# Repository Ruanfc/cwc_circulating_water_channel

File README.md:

# cwc_circulating_water_channel

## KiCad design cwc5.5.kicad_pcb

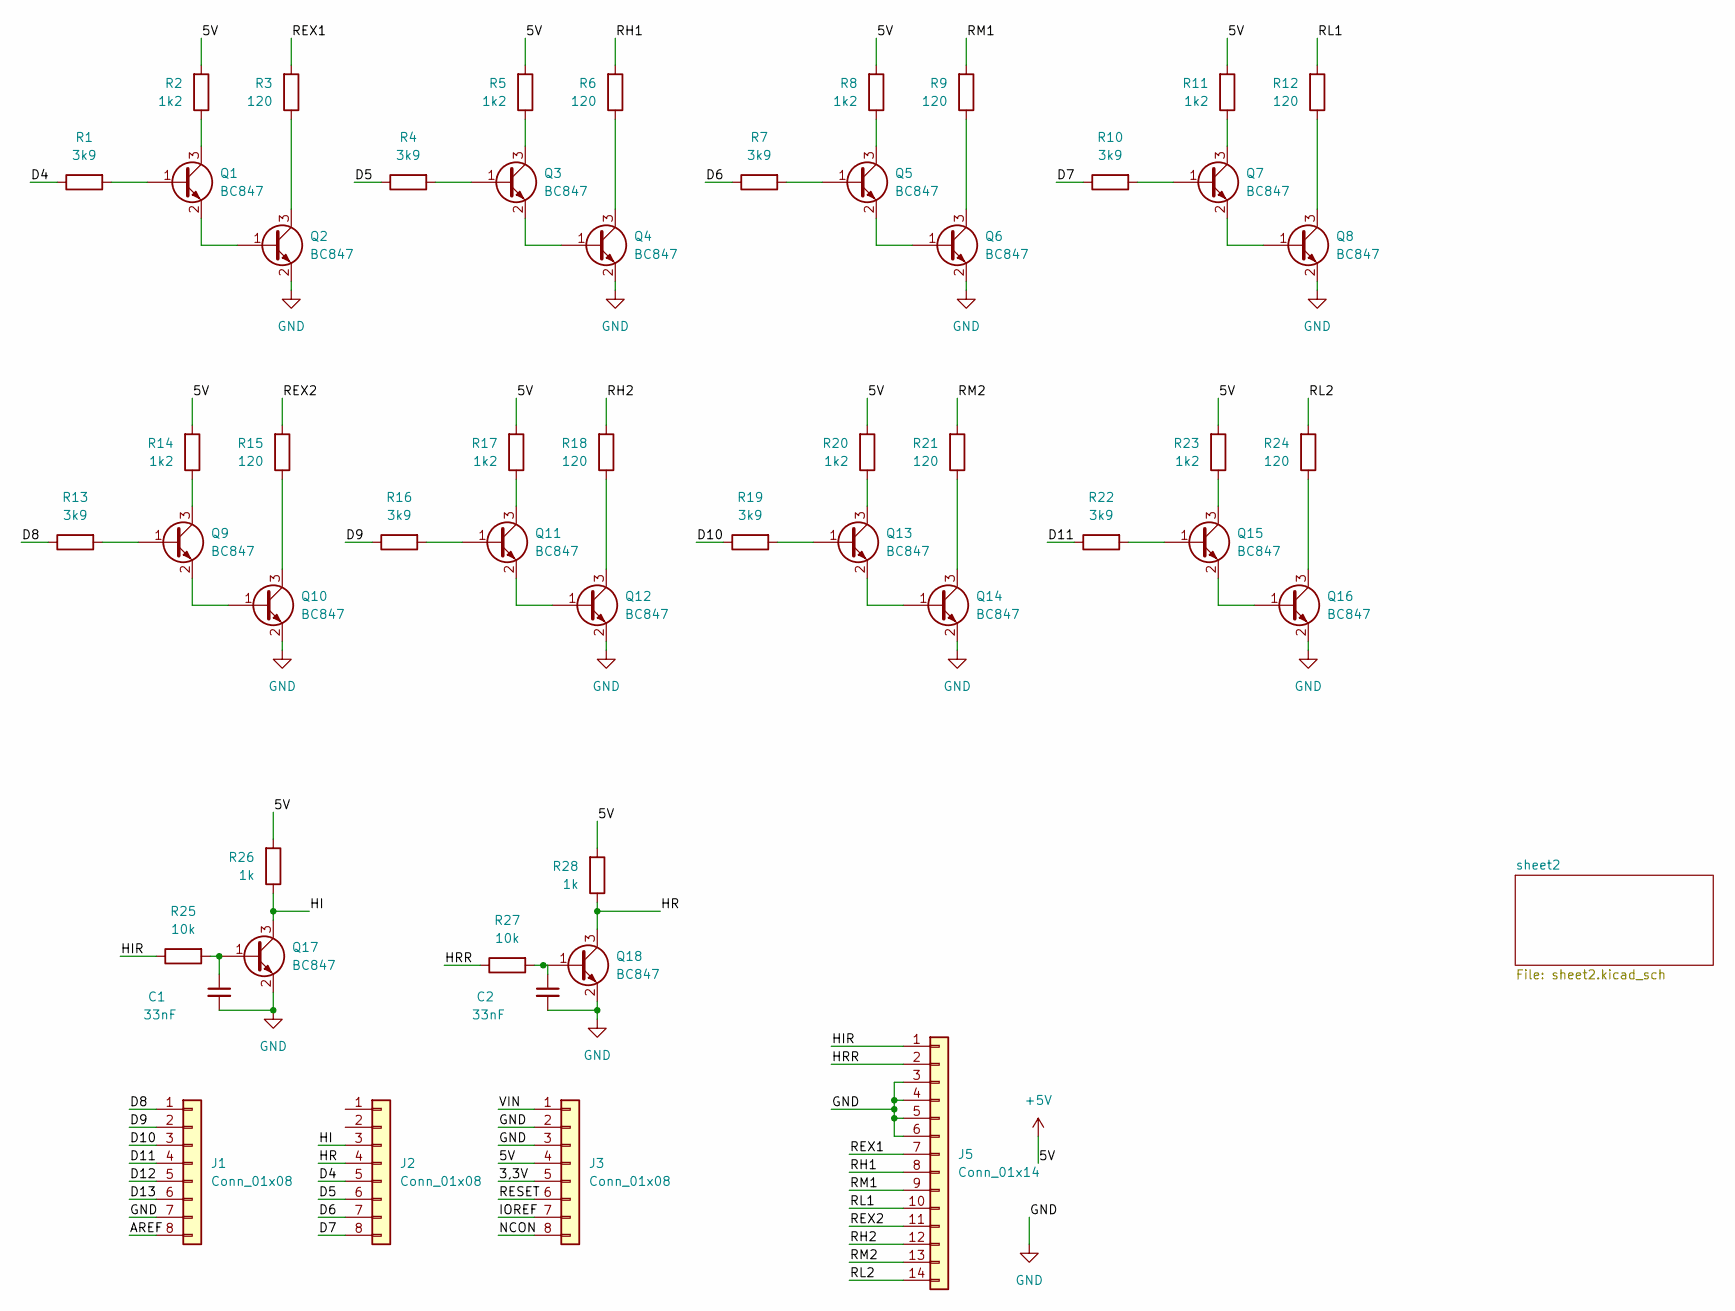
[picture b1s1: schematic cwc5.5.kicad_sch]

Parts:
C1, C2: 33nF; C_1206_3216Metric_Pad1.33x1.80mm_HandSolder
J1, J2, J3: Conn_01x08; PinHeader_1x08_P2.54mm_Vertical
J5: Conn_01x14; PinHeader_1x14_P2.54mm_Vertical
Q1, Q2, Q3, Q4, Q5, Q6, Q7, Q8, Q9, Q10, Q11, Q12, Q13, Q14, Q15, Q16, Q17, Q18: BC847; SOT-23_Handsoldering
R1, R4, R7, R10, R13, R16, R19, R22: 3k9; R_1206_3216Metric_Pad1.30x1.75mm_HandSolder
R2, R5, R8, R11, R14, R17, R20, R23: 1k2; R_1206_3216Metric_Pad1.30x1.75mm_HandSolder
R3, R6, R9, R12, R15, R18, R21, R24: 120; R_1206_3216Metric_Pad1.30x1.75mm_HandSolder
R25, R27: 10k; R_1206_3216Metric_Pad1.30x1.75mm_HandSolder
R26, R28: 1k; R_1206_3216Metric_Pad1.30x1.75mm_HandSolder

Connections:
+5V: J3.4, R2.2, R5.2, R8.2, R11.2, R14.2, R17.2, R20.2, R23.2, R26.2, R28.2
/3,3V: J3.5
/AREF: J1.8
/D4: J2.5, R1.1
/D5: J2.6, R4.1
/D6: J2.7, R7.1
/D7: J2.8, R10.1
/D8: J1.1, R13.1
/D9: J1.2, R16.1
/D10: J1.3, R19.1
/D11: J1.4, R22.1
/D12: J1.5
/D13: J1.6
/HI: J2.3, Q17.3 (C), R26.1
/HIR: J5.1, R25.1
/HR: J2.4, Q18.3 (C), R28.1
/HRR: J5.2, R27.1
/IOREF: J3.7
/NCON: J3.8
/RESET: J3.6
/REX1: J5.7, R3.2
/REX2: J5.11, R15.2
/RH1: J5.8, R6.2
/RH2: J5.12, R18.2
/RL1: J5.10, R12.2
/RL2: J5.14, R24.2
/RM1: J5.9, R9.2
/RM2: J5.13, R21.2
/VIN: J3.1
GND: C1.2, C2.2, J1.7, J3.2, J3.3, J5.3, J5.4, J5.5, J5.6, Q2.2 (E), Q4.2 (E), Q6.2 (E), Q8.2 (E), Q10.2 (E), Q12.2 (E), Q14.2 (E), Q16.2 (E), Q17.2 (E), Q18.2 (E); also elsewhere on the board
unnamed: C1.1, Q17.1 (B), R25.2
unnamed: C2.1, Q18.1 (B), R27.2
unnamed: Q1.1 (B), R1.2
unnamed: Q1.2 (E), Q2.1 (B)
unnamed: Q1.3 (C), R2.1
unnamed: Q2.3 (C), R3.1
unnamed: Q3.1 (B), R4.2
unnamed: Q3.2 (E), Q4.1 (B)
unnamed: Q3.3 (C), R5.1
unnamed: Q4.3 (C), R6.1
unnamed: Q5.1 (B), R7.2
unnamed: Q5.2 (E), Q6.1 (B)
unnamed: Q5.3 (C), R8.1
unnamed: Q6.3 (C), R9.1
unnamed: Q7.1 (B), R10.2
unnamed: Q7.2 (E), Q8.1 (B)
unnamed: Q7.3 (C), R11.1
unnamed: Q8.3 (C), R12.1
unnamed: Q9.1 (B), R13.2
unnamed: Q9.3 (C), R14.1
unnamed: Q9.2 (E), Q10.1 (B)
unnamed: Q10.3 (C), R15.1
unnamed: Q11.1 (B), R16.2
unnamed: Q11.2 (E), Q12.1 (B)
unnamed: Q11.3 (C), R17.1
unnamed: Q12.3 (C), R18.1
unnamed: Q13.1 (B), R19.2
unnamed: Q13.2 (E), Q14.1 (B)
unnamed: Q13.3 (C), R20.1
unnamed: Q14.3 (C), R21.1
unnamed: Q15.1 (B), R22.2
unnamed: Q15.2 (E), Q16.1 (B)
unnamed: Q15.3 (C), R23.1
unnamed: Q16.3 (C), R24.1

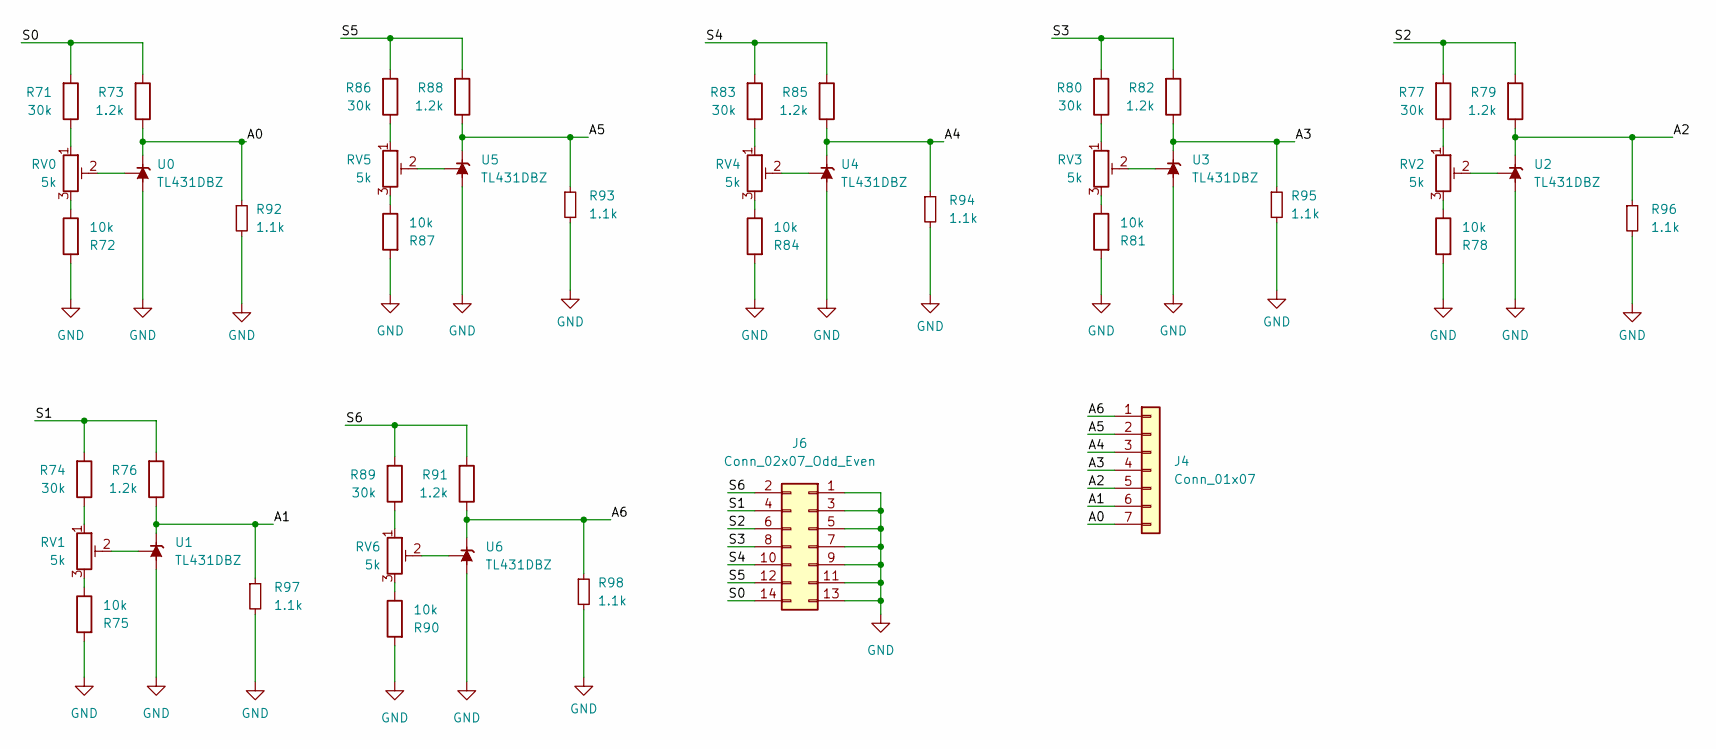
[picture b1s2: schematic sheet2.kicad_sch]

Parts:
J4: Conn_01x07; PinHeader_1x07_P2.54mm_Vertical
J6: Conn_02x07_Odd_Even; PinSocket_2x07_P2.54mm_Vertical
R71, R74, R77, R80, R83, R86, R89: 30k; R_1206_3216Metric_Pad1.30x1.75mm_HandSolder
R72, R75, R78, R81, R84, R87, R90: 10k; R_1206_3216Metric_Pad1.30x1.75mm_HandSolder
R73, R76, R91: 1.2k; R_1206_3216Metric_Pad1.30x1.75mm_HandSolder
R79, R82, R85, R88: 1.2k; R_Axial_DIN0207_L6.3mm_D2.5mm_P2.54mm_Vertical
R92, R93, R94, R95, R96, R97, R98: 1.1k; R_1206_3216Metric_Pad1.30x1.75mm_HandSolder
RV0, RV1, RV2, RV3, RV4, RV5, RV6: 5k; Potentiometer_Runtron_RM-065_Vertical
U0, U1, U2, U3, U4, U5, U6: TL431DBZ; SOT-23_Handsoldering

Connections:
/sheet2/A0: J4.7, R73.1, R92.1, U0.1 (K)
/sheet2/A1: J4.6, R76.1, R97.1, U1.1 (K)
/sheet2/A2: J4.5, R79.1, R96.1, U2.1 (K)
/sheet2/A3: J4.4, R82.1, R95.1, U3.1 (K)
/sheet2/A4: J4.3, R85.1, R94.1, U4.1 (K)
/sheet2/A5: J4.2, R88.1, R93.1, U5.1 (K)
/sheet2/A6: J4.1, R91.1, R98.1, U6.1 (K)
/sheet2/S0: J6.14, R71.2, R73.2
/sheet2/S1: J6.4, R74.2, R76.2
/sheet2/S2: J6.6, R77.2, R79.2
/sheet2/S3: J6.8, R80.2, R82.2
/sheet2/S4: J6.10, R83.2, R85.2
/sheet2/S5: J6.12, R86.2, R88.2
/sheet2/S6: J6.2, R89.2, R91.2
GND: J6.1, J6.3, J6.5, J6.7, J6.9, J6.11, J6.13, R72.2, R75.2, R78.2, R81.2, R84.2, R87.2, R90.2, R92.2, R93.2, R94.2, R95.2, R96.2, R97.2, R98.2, U0.3 (A), U1.3 (A), U2.3 (A), U3.3 (A), U4.3 (A), U5.3 (A), U6.3 (A); also elsewhere on the board
unnamed: R71.1, RV0.1
unnamed: R72.1, RV0.3
unnamed: R74.1, RV1.1
unnamed: R75.1, RV1.3
unnamed: R77.1, RV2.1
unnamed: R78.1, RV2.3
unnamed: R80.1, RV3.1
unnamed: R81.1, RV3.3
unnamed: R83.1, RV4.1
unnamed: R84.1, RV4.3
unnamed: R86.1, RV5.1
unnamed: R87.1, RV5.3
unnamed: R89.1, RV6.1
unnamed: R90.1, RV6.3
unnamed: RV0.2, U0.2 (REF)
unnamed: RV1.2, U1.2 (REF)
unnamed: RV2.2, U2.2 (REF)
unnamed: RV3.2, U3.2 (REF)
unnamed: RV4.2, U4.2 (REF)
unnamed: RV5.2, U5.2 (REF)
unnamed: RV6.2, U6.2 (REF)

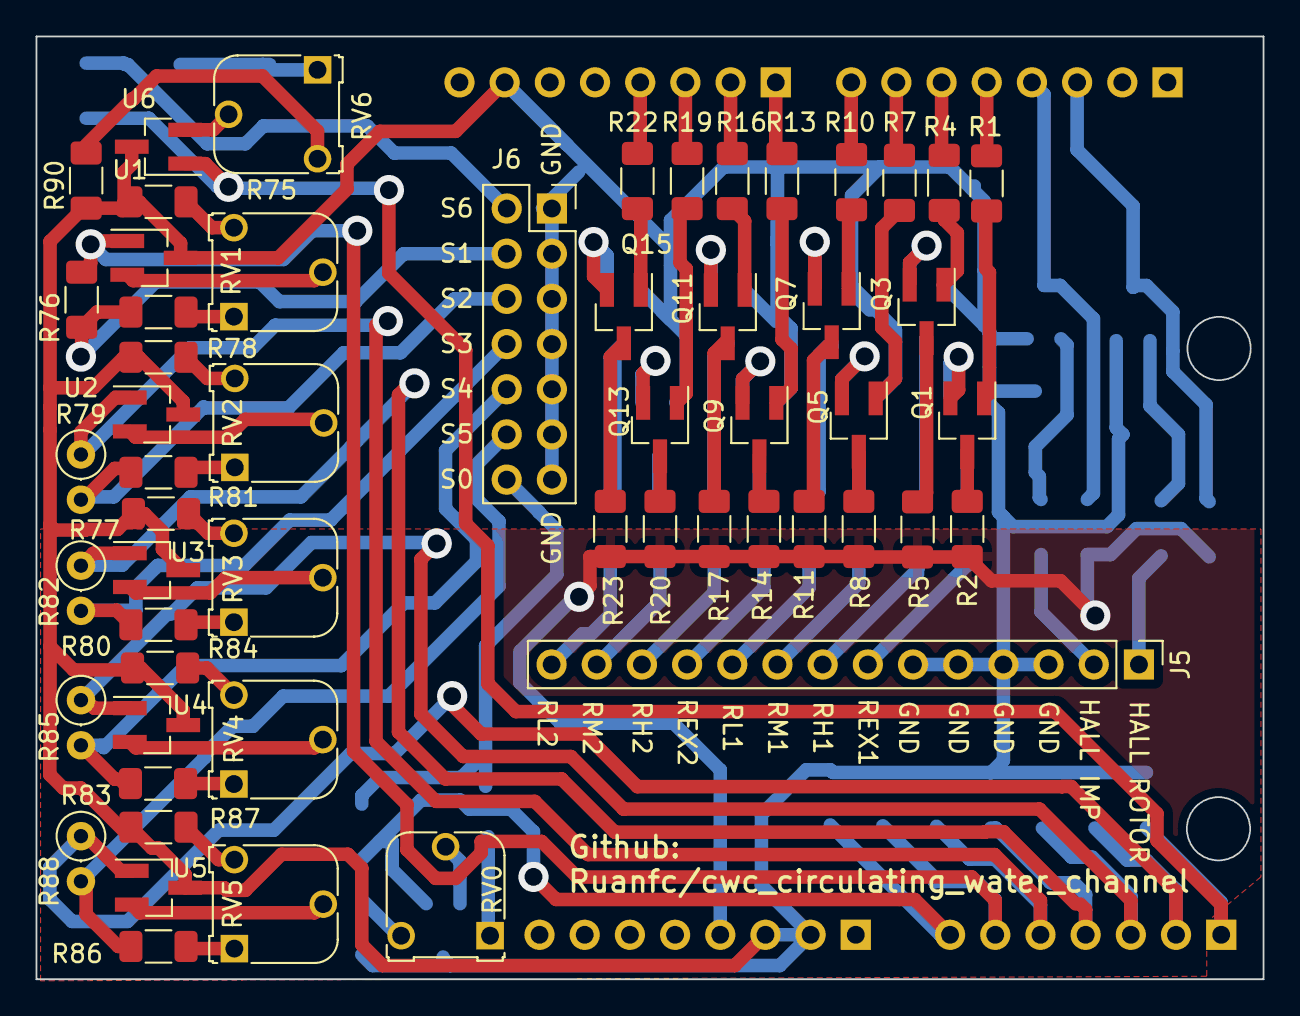
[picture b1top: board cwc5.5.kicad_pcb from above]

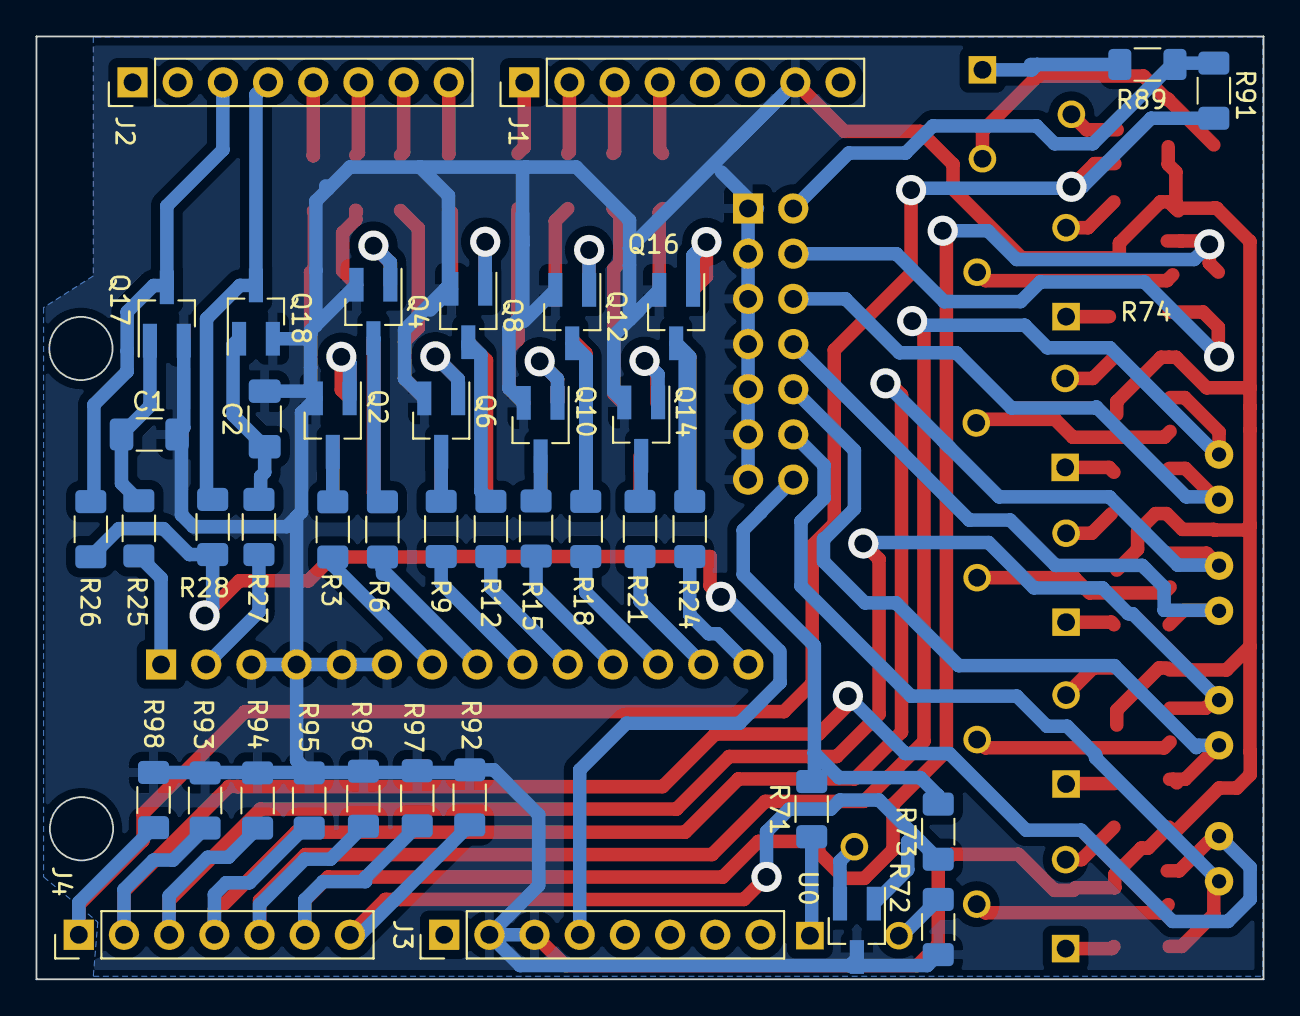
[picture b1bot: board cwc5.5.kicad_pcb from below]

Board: 2 copper layers, 69.0 x 53.0 mm, 96 parts (41 on the bottom side), 91 nets.

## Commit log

2022-04-09 projeto semicompleto
2022-04-09 Projeto enviado
